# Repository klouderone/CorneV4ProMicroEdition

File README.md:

# Corne V4 Pro-Micro Edition

This version of the Corne V4 is beginner friendly, adding support of the easier to solder through-hole diodes, with included support for wireless builds, and brings back the option to make your Corne with whatever microcontroller you want, with the updated V4 layout, which allows wireless support with a Nice!Nano V2, and ultimately save costs when ordering as you DO NOT need PCBA. 

The Corne V4 has a completely new board outline compared to the V3 and V2, and all further development for the Corne will be using the V4 outline.

I apologise if this repository is not fully organised/explained/complete.

Please contact me if you find something wrong. reddit: klouderone, discord: klouder#3331, email: claude@keaworkshop.com

## Features

- **SMD** & **Through-Hole** diode support
- **Wired and Wireless** Support with the inclusion of battery pads, battery connector, and battery switch
- Pro Micro Footprint Daughter Board Support
- **MX** Spaced
- Hotswap **MX & Choc V1** Support
- **Breakaway 6th column** for 5 column builds
- **OLED** & **Nice!View** support
- Waffle Pattern PCB

NOTE: Like all Split Keyboards, NEVER unplug the TRRS interconnect cable while your boards are connected to your computer. 

NOTE: Do not use the TRRS jack when also using a battery. ZMK does not support wired splits.

NOTE: Do not use a battery when using wired split. QMK does not support wireless, and the battery may cause damage to your microcontroller.

Please read the **entire repo** before using anything inside it.

Original Board designed by Foostan, modified By Kea Workshop.

Buy a Kit here https://www.keaworkshop.com/product/corne-v4-pro-micro-edition

https://github.com/foostan/crkbd

## Pictures

## Build 'Guide'

**Required Parts**

- 42x Kailh Choc V1 Hot Swap Sockets
- 42x Kailh MX Hot Swap Sockets
- 2x TRRS 3.5mm PJ-320A Audio Jack (if using non-wireless microcontroller)
- 42x 1N4148 SOD-123 Diodes
- 2x 3 Pin Toggle Switch (MSK-12C02 or PCM12SMTR)
- 2x Tactile Push Button Switch (3x6x4.3mm)
- 4x Mill-Max Machined 12 Pin Sockets
- 48x Mill-Max Machine Pins 
- 2x PH5 4 Pin Female Box Pin Header (for OLED)
- 2x PH5 5 Pin Female Box Pin Header (for Nice!View)
- 2x Microcontrollers (Pro Micro, Elite-C or Similar for wired, OR Nice!Nano V2 or similar for wireless)
- 2x Displays (.91 Inch OLED or Nice!View) (optional)
- 42x MX or Choc V1 Switches
- 42x MX or Choc V1 Keycaps
- 1x TRRS Male to Male Cable (if using non-wireless microcontroller)
- 2x Right Angle PH2 Battery Connector (if using a wireless microcontroller like the Nice!Nano V2)
- 2x Battery (if using a wireless microcontroller like the Nice!Nano V2) 

The build guide is **similar** to the video linked below, except without the LEDs, and the addition of the battery pads and battery switch.

The batteries are intended to be directly soldered to the board, however you can use a PH2 connector on extension leads and route it to the TRRS socket area if you would like to use a battery with a connector. I will change this so that there is also an included connector on the board on the next itteration.

Make sure you are confident will all steps before commencing build as a mistake could result in breaking your microcontroller. CHECK, CHECK AGAIN, AND THEN CHECK ONCE MORE.

https://www.youtube.com/watch?v=vzDTdLaAzXc

## Cases

The enclosed case uses 7mm M2 standoffs, for both the PCB and the oled covers. 

Ordering/Printing: Each Case has its own folder, and all parts needed for each case are located in that folder. 

Due to the new outline of the corne V4, unfortunately all previous corne version cases are incompatible.

In the cases directory, there are options for a fully enclosed case, or just a bottom plate with open sides. 

NOTE: due to the placement of the pro micro and TRRS jack, the cases for the v4 on foostans repository are NOT COMPATIBLE with the Pro Micro Edition of the corne v4, as the usb and TRRS jack are blocked by the case as they are specifically placed holes. 

The pro micro edition cases were designed to be as minimalist as possible, so they do have thin parts. This may cause a problem when ordering through JLC, as they have a minimum reccommended thickness of around 1.25mm. I have never had a problem printing all the files myself. 

The enclosed case with folding tenting leg pockets use the following folding legs. https://www.keaworkshop.com/category/components/product/case-tenting-legs

## Firmware 

No external firmware is needed, the same firmware found on the VIAL and QMK repos for the Corne V2 will work for this PCB.

## Changelog

### Revision 1 to Revision 2 - 16/02/25
- Added support for battery connector
- Added hole for under-board battery support
- Moved OLED headers .5mm lower for easier under microcontroller battery routing.
- Made under microcontroller hole larger
- Added support for through hole diodes
- Moved TRRS jack 2mm lower
- Updated Cases to match revision change
- Diodes have been relocated
- Added TPU sound dampener plate
- Added Rev 1 to Archive for back support

## Legal

THE SOFTWARE IS PROVIDED "AS IS", WITHOUT WARRANTY OF ANY KIND, EXPRESS OR IMPLIED, INCLUDING BUT NOT LIMITED TO THE WARRANTIES OF MERCHANTABILITY, FITNESS FOR A PARTICULAR PURPOSE AND NONINFRINGEMENT. IN NO EVENT SHALL THE AUTHORS OR COPYRIGHT HOLDERS BE LIABLE FOR ANY CLAIM, DAMAGES OR OTHER LIABILITY, WHETHER IN AN ACTION OF CONTRACT, TORT OR OTHERWISE, ARISING FROM, OUT OF OR IN CONNECTION WITH THE SOFTWARE OR THE USE OR OTHER DEALINGS IN THE SOFTWARE.

## Revision Control

Rev 1 - Archived 16/02/2025

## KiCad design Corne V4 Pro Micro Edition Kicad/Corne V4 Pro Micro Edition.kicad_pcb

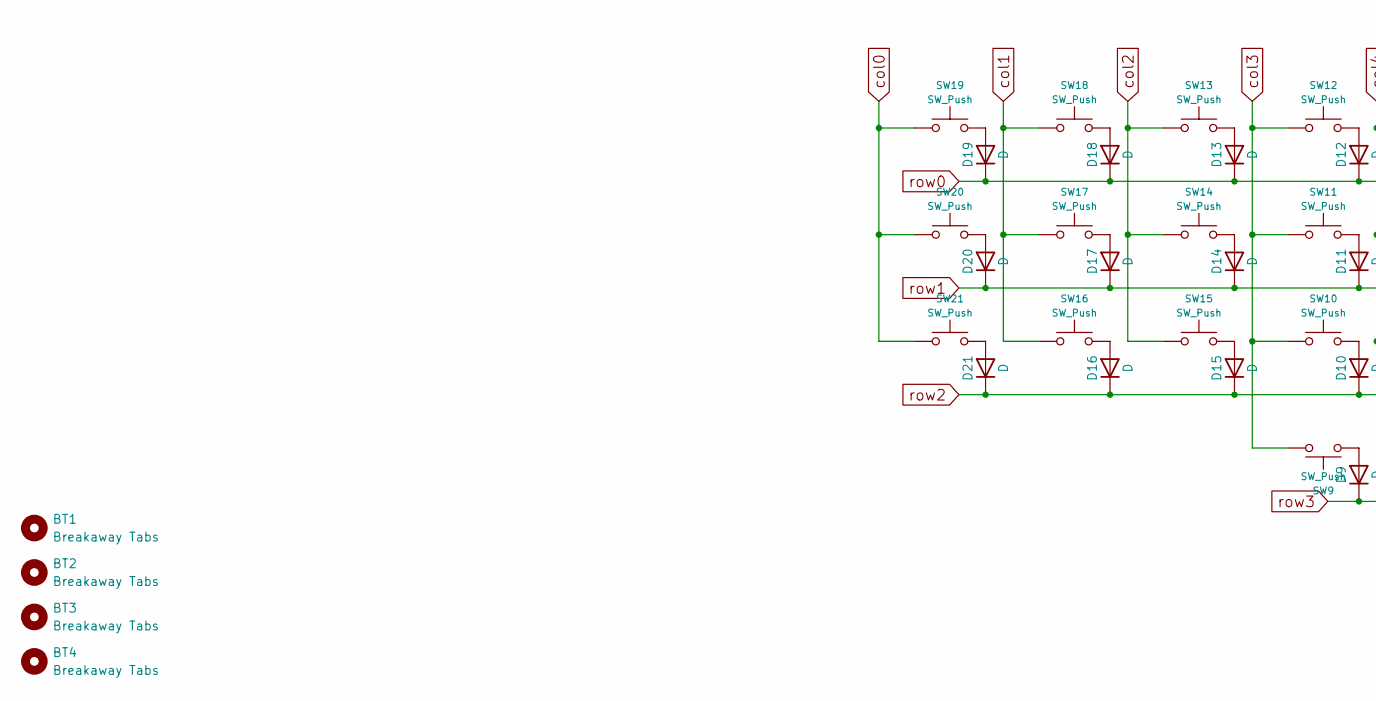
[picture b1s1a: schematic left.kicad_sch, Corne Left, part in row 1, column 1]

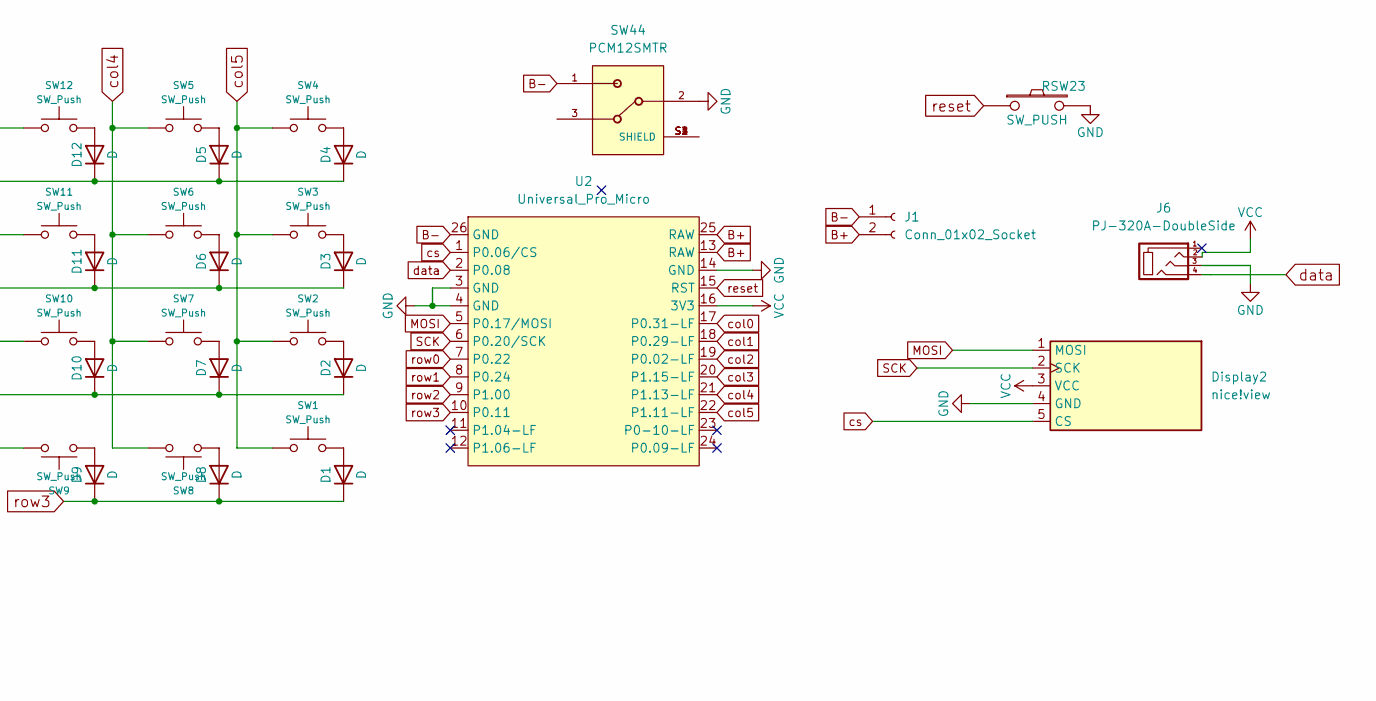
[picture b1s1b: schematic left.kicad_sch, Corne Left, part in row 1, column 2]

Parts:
BT1, BT2, BT3, BT4: Breakaway Tabs; Breakaway_Tabs
D1, D2, D3, D4, D5, D6, D7, D8, D9, D10, D11, D12, D13, D14, D15, D16, D17, D18, D19, D20, D21: D; SMD_SOD123
Display2: nice!view; nice_view
J1: Conn_01x02_Socket; PH_S2B-PH2-K_1x02_P2.00mm_Horizontal
J6: PJ-320A-DoubleSide; TRRS-PJ-320A
RSW23: SW_PUSH; Reset_3x6x4.3
SW1, SW2, SW3, SW4, SW5, SW6, SW7, SW8, SW9, SW10, SW11, SW12, SW13, SW14, SW15, SW16, SW17, SW18, SW19, SW20, SW21: SW_Push; SW_MXchoc_HS_1u
SW44: PCM12SMTR; MSK-12C02 Toggle Switch
U2: Universal_Pro_Micro; Pro_Micro_Footprint_CornePME

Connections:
B+: J1.2, U2.13 (RAW), U2.25 (RAW)
B-: J1.1, SW44.1, U2.26 (GND)
GND: Display2.4 (GND), J6.3, RSW23.2, SW44.2, U2.3 (GND), U2.4 (GND), U2.14 (GND)
MOSI: Display2.1 (MOSI), U2.5 (P0.17/MOSI)
unnamed: D1.2 (A), SW1.2
unnamed: D2.2 (A), SW2.2
unnamed: D3.2 (A), SW3.2
unnamed: D4.2 (A), SW4.2
unnamed: D5.2 (A), SW5.2
unnamed: D6.2 (A), SW6.2
unnamed: D7.2 (A), SW7.2
unnamed: D8.2 (A), SW8.1
unnamed: D9.2 (A), SW9.1
unnamed: D10.2 (A), SW10.2
unnamed: D11.2 (A), SW11.2
unnamed: D12.2 (A), SW12.2
unnamed: D13.2 (A), SW13.2
unnamed: D14.2 (A), SW14.2
unnamed: D15.2 (A), SW15.2
unnamed: D16.2 (A), SW16.2
unnamed: D17.2 (A), SW17.2
unnamed: D18.2 (A), SW18.2
unnamed: D19.2 (A), SW19.2
unnamed: D20.2 (A), SW20.2
unnamed: D21.2 (A), SW21.2
SCK: Display2.2 (SCK), U2.6 (P0.20/SCK)
VCC: Display2.3 (VCC), J6.2, U2.16 (3V3)
col0: SW19.1, SW20.1, SW21.1, U2.17 (P0.31-LF)
col1: SW16.1, SW17.1, SW18.1, U2.18 (P0.29-LF)
col2: SW13.1, SW14.1, SW15.1, U2.19 (P0.02-LF)
col3: SW9.2, SW10.1, SW11.1, SW12.1, U2.20 (P1.15-LF)
col4: SW5.1, SW6.1, SW7.1, SW8.2, U2.21 (P1.13-LF)
col5: SW1.1, SW2.1, SW3.1, SW4.1, U2.22 (P1.11-LF)
cs: Display2.5 (CS), U2.1 (P0.06/CS)
data: J6.4, U2.2 (P0.08)
reset: RSW23.1, U2.15 (RST)
row0: D4.1 (K), D5.1 (K), D12.1 (K), D13.1 (K), D18.1 (K), D19.1 (K), U2.7 (P0.22)
row1: D3.1 (K), D6.1 (K), D11.1 (K), D14.1 (K), D17.1 (K), D20.1 (K), U2.8 (P0.24)
row2: D2.1 (K), D7.1 (K), D10.1 (K), D15.1 (K), D16.1 (K), D21.1 (K), U2.9 (P1.00)
row3: D1.1 (K), D8.1 (K), D9.1 (K), U2.10 (P0.11)

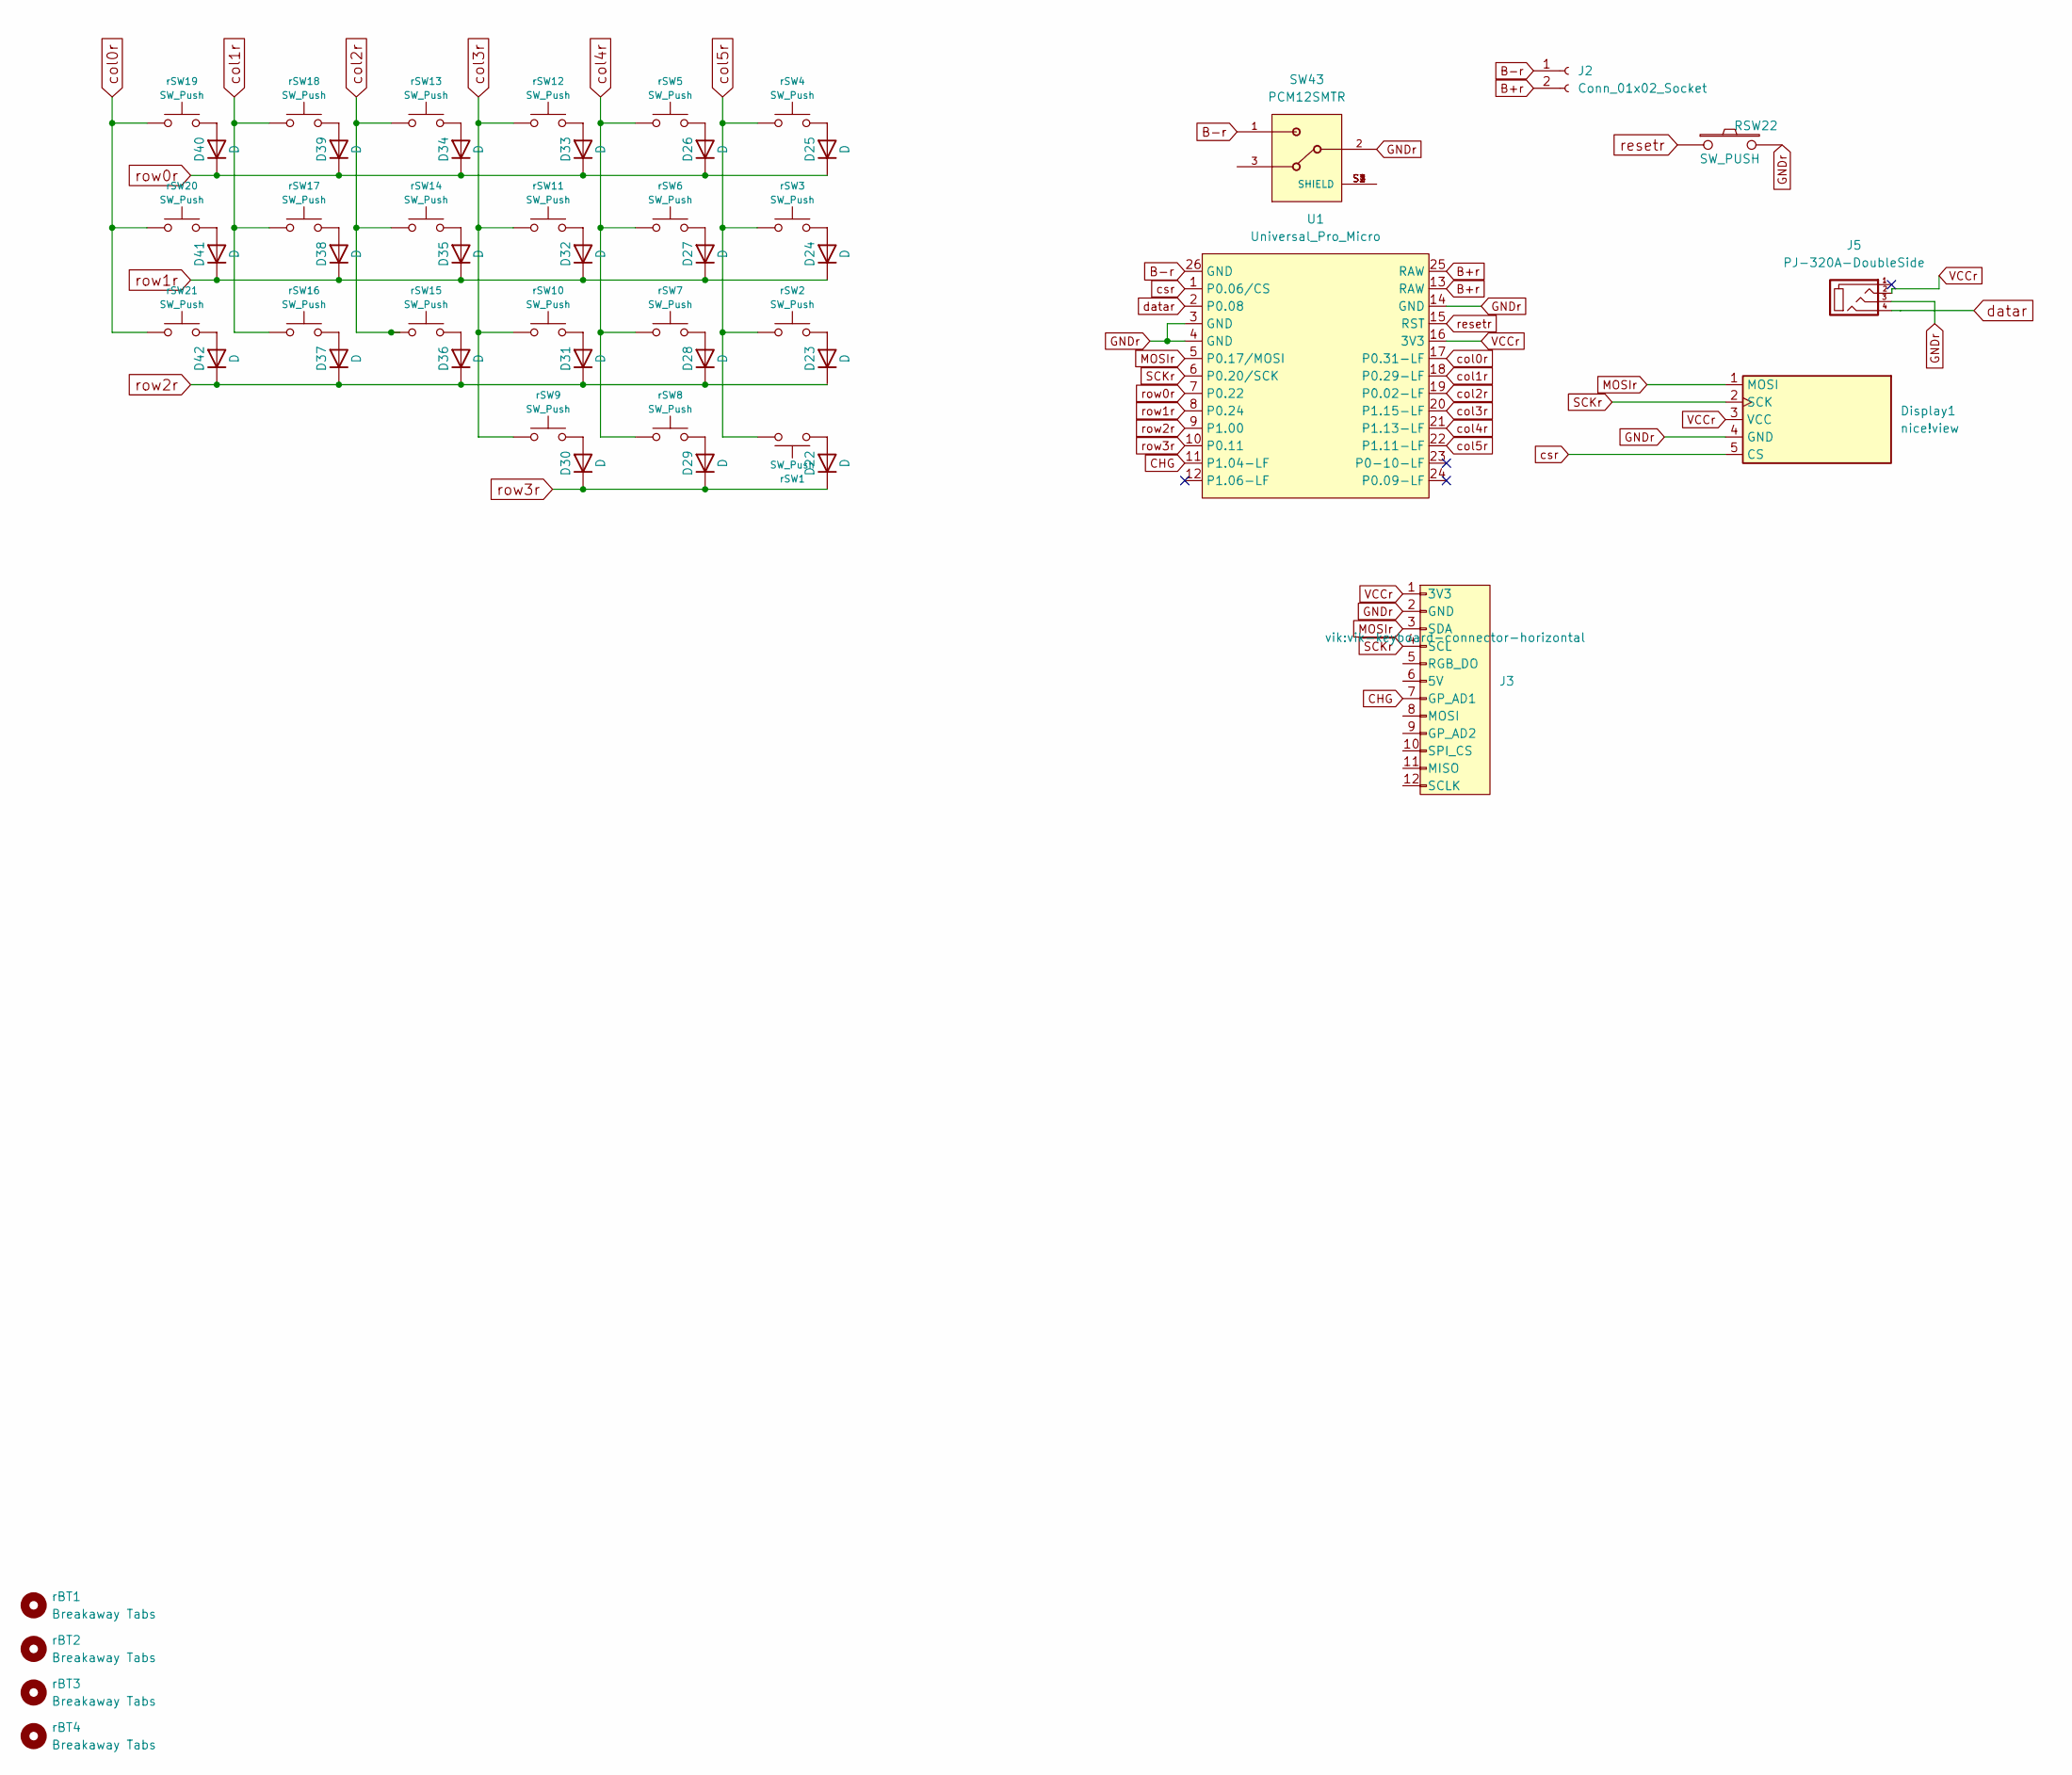
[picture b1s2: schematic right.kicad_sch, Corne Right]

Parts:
D22, D23, D24, D25, D26, D27, D28, D29, D30, D31, D32, D33, D34, D35, D36, D37, D38, D39, D40, D41, D42: D; SMD_SOD123
Display1: nice!view; nice_view
J2: Conn_01x02_Socket; PH_S2B-PH2-K_1x02_P2.00mm_Horizontal
J3: vik-keyboard-connector-horizontal
J5: PJ-320A-DoubleSide; TRRS-PJ-320A
RSW22: SW_PUSH; Reset_3x6x4.3
SW43: PCM12SMTR; MSK-12C02 Toggle Switch
U1: Universal_Pro_Micro; Pro_Micro_Footprint_CornePME
rBT1, rBT2, rBT3, rBT4: Breakaway Tabs; Breakaway_Tabs
rSW1, rSW2, rSW3, rSW4, rSW5, rSW6, rSW7, rSW8, rSW9, rSW10, rSW11, rSW12, rSW13, rSW14, rSW15, rSW16, rSW17, rSW18, rSW19, rSW20, rSW21: SW_Push; SW_MXchoc_HS_1u

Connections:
B+r: J2.2, U1.13 (RAW), U1.25 (RAW)
B-r: J2.1, SW43.1, U1.26 (GND)
CHG: J3.7 (GP_AD1), U1.11 (P1.04-LF)
GNDr: Display1.4 (GND), J3.2 (GND), J5.3, RSW22.2, SW43.2, U1.3 (GND), U1.4 (GND), U1.14 (GND)
MOSIr: Display1.1 (MOSI), J3.3 (SDA), U1.5 (P0.17/MOSI)
unnamed: D22.2 (A), rSW1.1
unnamed: D23.2 (A), rSW2.2
unnamed: D24.2 (A), rSW3.2
unnamed: D25.2 (A), rSW4.2
unnamed: D26.2 (A), rSW5.2
unnamed: D27.2 (A), rSW6.2
unnamed: D28.2 (A), rSW7.2
unnamed: D29.2 (A), rSW8.2
unnamed: D30.2 (A), rSW9.2
unnamed: D31.2 (A), rSW10.2
unnamed: D32.2 (A), rSW11.2
unnamed: D33.2 (A), rSW12.2
unnamed: D34.2 (A), rSW13.2
unnamed: D35.2 (A), rSW14.2
unnamed: D36.2 (A), rSW15.2
unnamed: D37.2 (A), rSW16.2
unnamed: D38.2 (A), rSW17.2
unnamed: D39.2 (A), rSW18.2
unnamed: D40.2 (A), rSW19.2
unnamed: D41.2 (A), rSW20.2
unnamed: D42.2 (A), rSW21.2
SCKr: Display1.2 (SCK), J3.4 (SCL), U1.6 (P0.20/SCK)
VCCr: Display1.3 (VCC), J3.1 (3V3), J5.2, U1.16 (3V3)
col0r: U1.17 (P0.31-LF), rSW19.1, rSW20.1, rSW21.1
col1r: U1.18 (P0.29-LF), rSW16.1, rSW17.1, rSW18.1
col2r: U1.19 (P0.02-LF), rSW13.1, rSW14.1, rSW15.1
col3r: U1.20 (P1.15-LF), rSW9.1, rSW10.1, rSW11.1, rSW12.1
col4r: U1.21 (P1.13-LF), rSW5.1, rSW6.1, rSW7.1, rSW8.1
col5r: U1.22 (P1.11-LF), rSW1.2, rSW2.1, rSW3.1, rSW4.1
csr: Display1.5 (CS), U1.1 (P0.06/CS)
datar: J5.4, U1.2 (P0.08)
resetr: RSW22.1, U1.15 (RST)
row0r: D25.1 (K), D26.1 (K), D33.1 (K), D34.1 (K), D39.1 (K), D40.1 (K), U1.7 (P0.22)
row1r: D24.1 (K), D27.1 (K), D32.1 (K), D35.1 (K), D38.1 (K), D41.1 (K), U1.8 (P0.24)
row2r: D23.1 (K), D28.1 (K), D31.1 (K), D36.1 (K), D37.1 (K), D42.1 (K), U1.9 (P1.00)
row3r: D22.1 (K), D29.1 (K), D30.1 (K), U1.10 (P0.11)

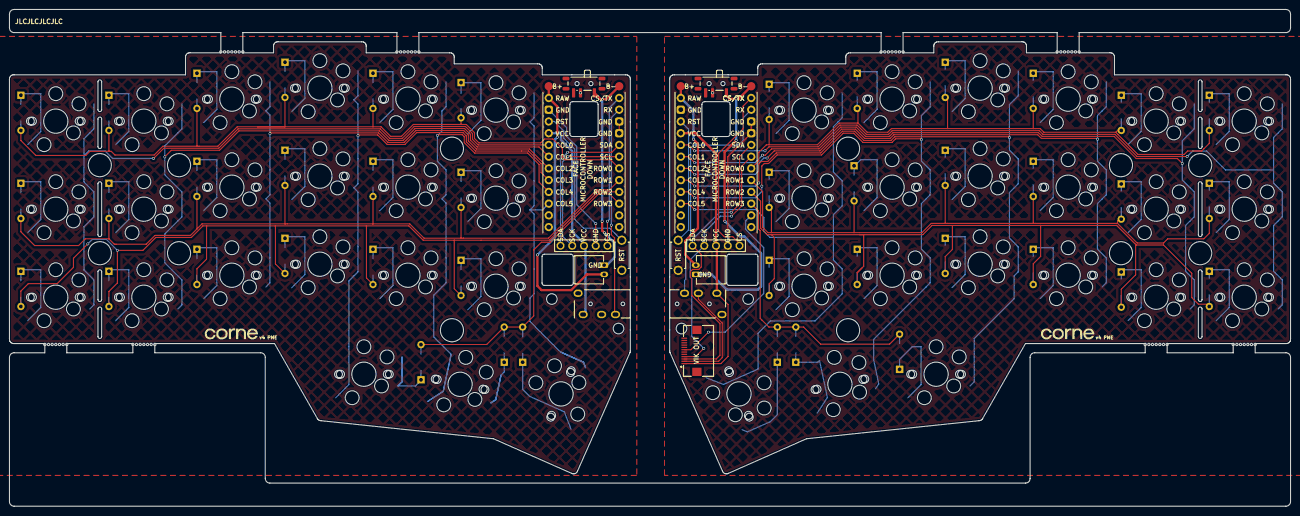
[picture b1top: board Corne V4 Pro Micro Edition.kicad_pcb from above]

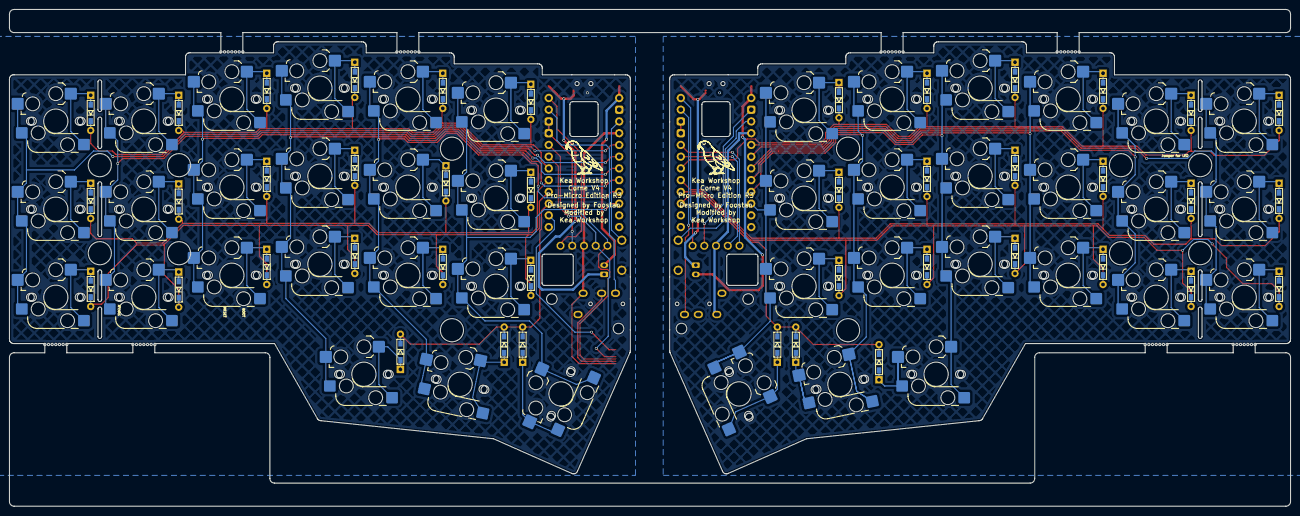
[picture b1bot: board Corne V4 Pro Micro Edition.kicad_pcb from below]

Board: 2 copper layers, 277.2 x 107.4 mm, 107 parts (86 on the bottom side), 81 nets.

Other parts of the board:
Ref**: Val**; thread_m2
Ref**#2: Val**; thread_m2

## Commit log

2024-05-01 Kicad and Gerber File Addition
2024-08-12 Changed OLED cover hole locations
2024-09-04 Added Folding Tenting Feet Enclosed Case Option
2024-09-06 Battery Hole, OLED Hole update
    changed location of OLED hole to match switch plate, added a hole for leads for a connector battery to pass through
2024-09-07 Increased size of battery switch pads
2024-09-07 Upload updated production files
2024-09-07 increased size of smd diode pads
2024-09-07 updated production files
2024-09-07 updated tenting case
2024-10-01 Organise Case Directory, Switch Plate Additions
    added Choc Specific Switch Plates
2024-10-07 save with kicad 8
2024-10-07 add logo and copper zone (copied from main PCB)
2024-10-07 regenerated production file I've followed this guide https://jlcpcb.com/help/article/how-to-generate-gerber-and-drill-files-in-kicad-8
2024-12-15 added SVG acrylic cover files
2024-12-19 Add SVG acrylic bottom plate files Exported SVG from FreeCAD, and removed redundant paths in Illustrator.
2024-12-19 Add SVG acrylic switch plate files Exported SVG from FreeCAD, and removed redundant paths in Illustrator. MX and choc can share the same switch plate if the number of column is the same.
2024-12-19 Fix wrong OLED SVG dimension The .svg files for OLED cover has wrong dimension when imported to Illustrator. No need both sides as acrylic can be flipped.
2025-02-16 Archiving Revision 1
    Archiving Revision 1 in prep for Revision 2 Upload
2025-02-16 Upload of Rev 2
    Upload of Rev 2 with requested changes and additional ones. Check changelog on the README.
2025-10-21 Case Modification
    fixing unaligned TRRS cutout
2025-11-02 Adding VIK Connector to support Procyon
    Procyon (https://github.com/george-norton/procyon?tab=readme-ov-file) is
    open-source touchpad module, the ideia is to have the option to use it
    or the display on the right side, this can work with ZMK but not on
    macos, QMK has full support so is a better option
2025-11-02 removing 3.3v text from the pcb
